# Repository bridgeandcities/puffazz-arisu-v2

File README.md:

# puffazz-arisu-v2
Custom PCB for the Arisu keyboard with LED underglow and USB-C support.

Based from https://github.com/FateNozomi/arisu-pcb

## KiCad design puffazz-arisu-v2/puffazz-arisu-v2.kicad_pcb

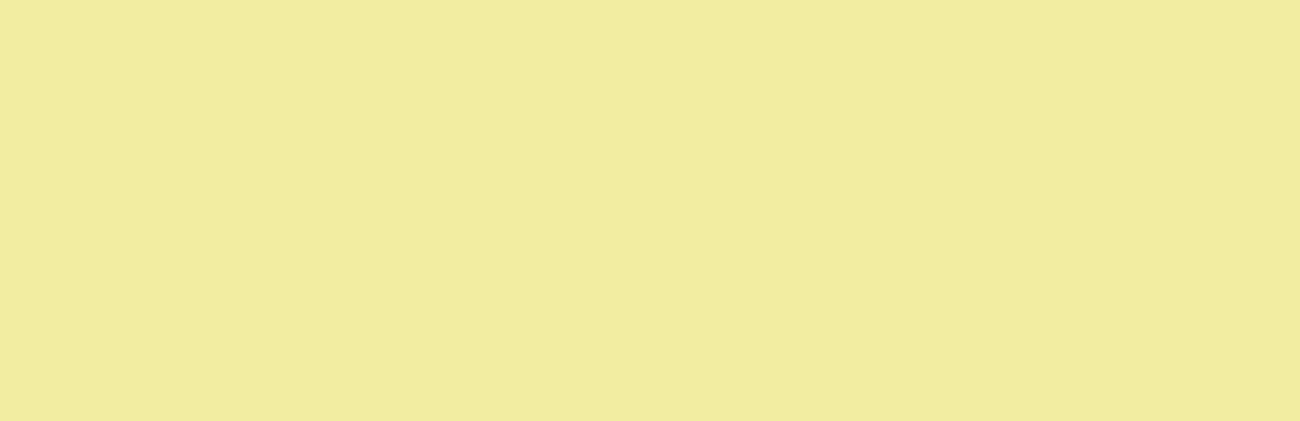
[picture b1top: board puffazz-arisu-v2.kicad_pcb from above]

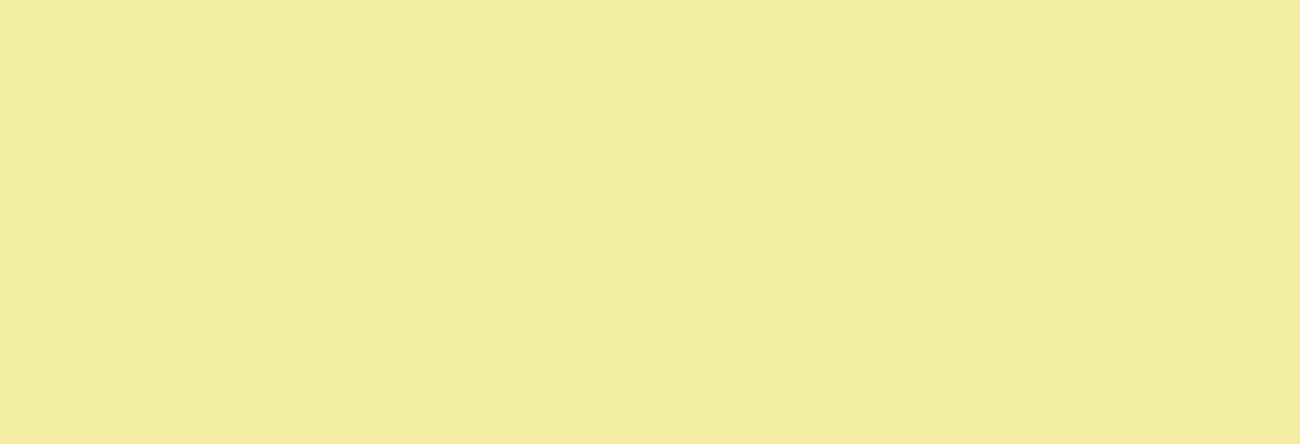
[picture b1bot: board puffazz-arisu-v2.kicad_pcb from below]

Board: 2 copper layers, 96 parts (25 on the bottom side), 39 nets, no tracks yet.

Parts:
C18: 0.1uF; C_0805_2012Metric
D69, D70, D71, D72, D73, D74, D75, D76, D77, D78, D79, D80, D81, D82: WS2812B; LED_WS2812B_PLCC4_5.0x5.0mm_P3.2mm
MX_: SW_Cherry_MX_1.00u_PCB
MX_#0, MX_#1, MX_#2, MX_#3, MX_#4, MX_#5, MX_#6, MX_#7, MX_#8, MX_#9: MX-NoLED; SW_Cherry_MX_1.00u_PCB
MX_#+1: MX-NoLED; SW_Cherry_MX_1.00u_PCB
MX_#-1: MX-NoLED; SW_Cherry_MX_1.00u_PCB
MX_#BKSP2: MX-NoLED; SW_Cherry_MX_2.00u_PCB
MX_#PGUP1: MX-NoLED; SW_Cherry_MX_1.00u_PCB
MX_#TAB1: MX-NoLED; SW_Cherry_MX_1.50u_PCB
MX_#`1: MX-NoLED; SW_Cherry_MX_1.00u_PCB
MX_#|1: MX-NoLED; SW_Cherry_MX_1.00u_PCB
MX_:1: MX-NoLED; SW_Cherry_MX_1.00u_PCB
MX_<1: MX-NoLED; SW_Cherry_MX_1.00u_PCB
MX_>1: MX-NoLED; SW_Cherry_MX_1.00u_PCB
MX_?1: MX-NoLED; SW_Cherry_MX_1.00u_PCB
MX_A1: MX-NoLED; SW_Cherry_MX_1.00u_PCB
MX_B1: MX-NoLED; SW_Cherry_MX_1.00u_PCB
MX_BCKSP1: MX-NoLED; SW_Cherry_MX_1.50u_PCB
MX_C1: MX-NoLED; SW_Cherry_MX_1.00u_PCB
MX_CAPS1: MX-NoLED; SW_Cherry_MX_1.75u_PCB
MX_CAPS2: MX-NoLED; SW_Cherry_MX_1.00u_PCB
MX_D1: MX-NoLED; SW_Cherry_MX_1.00u_PCB
MX_DOWN1: MX-NoLED; SW_Cherry_MX_1.00u_PCB
MX_E1: MX-NoLED; SW_Cherry_MX_1.00u_PCB
MX_ESC1: MX-NoLED; SW_Cherry_MX_1.00u_PCB
MX_F1: MX-NoLED; SW_Cherry_MX_1.00u_PCB
MX_FN1: MX-NoLED; SW_Cherry_MX_1.00u_PCB
MX_G1: MX-NoLED; SW_Cherry_MX_1.00u_PCB
MX_H1: MX-NoLED; SW_Cherry_MX_1.00u_PCB
MX_I1: MX-NoLED; SW_Cherry_MX_1.00u_PCB
MX_J1: MX-NoLED; SW_Cherry_MX_1.00u_PCB
MX_K1: MX-NoLED; SW_Cherry_MX_1.00u_PCB
MX_L1: MX-NoLED; SW_Cherry_MX_1.00u_PCB
MX_LALT1: MX-NoLED; SW_Cherry_MX_1.25u_PCB
MX_LALT2: MX-NoLED; SW_Cherry_MX_1.50u_PCB
MX_LCTRL1: MX-NoLED; SW_Cherry_MX_1.50u_PCB
MX_LEFT1: MX-NoLED; SW_Cherry_MX_1.00u_PCB
MX_LSHIFT1: MX-NoLED; SW_Cherry_MX_2.25u_PCB
MX_LWIN1: MX-NoLED; SW_Cherry_MX_1.00u_PCB
MX_M1: MX-NoLED; SW_Cherry_MX_1.00u_PCB
MX_N1: MX-NoLED; SW_Cherry_MX_1.00u_PCB
MX_O1: MX-NoLED; SW_Cherry_MX_1.00u_PCB
MX_P1: MX-NoLED; SW_Cherry_MX_1.00u_PCB
MX_PGDN1: MX-NoLED; SW_Cherry_MX_1.00u_PCB
MX_Q1: MX-NoLED; SW_Cherry_MX_1.00u_PCB
MX_R1: MX-NoLED; SW_Cherry_MX_1.00u_PCB
MX_RALT1: MX-NoLED; SW_Cherry_MX_1.50u_PCB
MX_RETURN1: MX-NoLED; SW_Cherry_MX_2.25u_PCB_Flipped
MX_RIGHT1: MX-NoLED; SW_Cherry_MX_1.00u_PCB
MX_RSHIFT1: MX-NoLED; SW_Cherry_MX_1.75u_PCB
MX_S1: MX-NoLED; SW_Cherry_MX_1.00u_PCB
MX_SPACE1: MX-NoLED; SW_Cherry_MX_2.00u_PCB_Flipped
MX_SPACE2: MX-NoLED; SW_Cherry_MX_2.25u_PCB_Flipped
MX_SPACE3: MX-NoLED; SW_Cherry_MX_2.75u_PCB_Flipped
MX_T1: MX-NoLED; SW_Cherry_MX_1.00u_PCB
MX_U1: MX-NoLED; SW_Cherry_MX_1.00u_PCB
MX_UP1: MX-NoLED; SW_Cherry_MX_1.00u_PCB
MX_V1: MX-NoLED; SW_Cherry_MX_1.00u_PCB
MX_W1: MX-NoLED; SW_Cherry_MX_1.00u_PCB
MX_X1: MX-NoLED; SW_Cherry_MX_1.00u_PCB
MX_Y1: MX-NoLED; SW_Cherry_MX_1.00u_PCB
MX_Z1: MX-NoLED; SW_Cherry_MX_1.00u_PCB
MX_[1: MX-NoLED; SW_Cherry_MX_1.00u_PCB
MX_]1: MX-NoLED; SW_Cherry_MX_1.00u_PCB
R1, R2: 10k; R_0805_2012Metric
R3, R4: 5.1k; R_0805_2012Metric
R5, R6: 22; R_0805_2012Metric
SW1: SW_Push; SW_SPST_SKQG_WithStem
U1: ATmega32U4-AU; TQFP-44_10x10mm_P0.8mm
USB1: HRO-TYPE-C-31-M-12; HRO-TYPE-C-31-M-12-Assembly
Y1: 16MHz; Crystal_SMD_3225-4Pin_3.2x2.5mm_HandSoldering

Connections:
+5V: C18.1, D69.1, D70.1, D71.1, D72.1, D73.1, D74.1, D75.1, D76.1, D77.1, D78.1, D79.1, D80.1, D81.1, D82.1, R1.2, U1.2, U1.7, U1.14, U1.24, U1.34, U1.44
COL0: MX_#1.1, MX_#TAB1.1, MX_A1.1, MX_CAPS1.1, MX_CAPS2.1, MX_ESC1.1, MX_LCTRL1.1, MX_LSHIFT1.1, MX_Q1.1, MX_Z1.1, U1.41
COL1: MX_#2.1, MX_#3.1, MX_C1.1, MX_D1.1, MX_E1.1, MX_LALT1.1, MX_LALT2.1, MX_S1.1, MX_W1.1, MX_X1.1, U1.40
COL2: MX_#4.1, MX_#5.1, MX_B1.1, MX_F1.1, MX_G1.1, MX_LWIN1.1, MX_R1.1, MX_SPACE1.1, MX_SPACE2.1, MX_T1.1, MX_V1.1, U1.39
COL3: MX_#6.1, MX_#7.1, MX_H1.1, MX_J1.1, MX_M1.1, MX_N1.1, MX_SPACE3.1, MX_U1.1, MX_Y1.1, U1.27
COL4: MX_#8.1, MX_#9.1, MX_<1.1, MX_>1.1, MX_I1.1, MX_K1.1, MX_L1.1, MX_O1.1, MX_RALT1.1, U1.21
COL5: MX_#0.1, MX_#-1.1, MX_:1.1, MX_?1.1, MX_LEFT1.1, MX_P1.1, MX_RSHIFT1.1, MX_[1.1, U1.20
COL6: MX_#+1.1, MX_#`1.1, MX_DOWN1.1, MX_RETURN1.1, MX_UP1.1, MX_]1.1, U1.19
COL7: MX_#BKSP2.1, MX_#PGUP1.1, MX_#|1.1, MX_BCKSP1.1, MX_FN1.1, MX_PGDN1.1, MX_RIGHT1.1, U1.18
D+: R5.2, U1.4
D-: R6.2, U1.3
GND: C18.2, D69.3, D70.3, D71.3, D72.3, D73.3, D74.3, D75.3, D76.3, D77.3, D78.3, D79.3, D80.3, D81.3, D82.3, R2.1, R3.1, R4.1, SW1.1, U1.5, U1.15, U1.23, U1.35, U1.43, USB1.1, USB1.12, USB1.13, Y1.2, Y1.4
unnamed: U1.17, Y1.1
unnamed: U1.16, Y1.3
unnamed: R5.1, USB1.5, USB1.7
unnamed: R6.1, USB1.6, USB1.8
unnamed: MX_#BKSP2.2, MX_#|1.2
unnamed: MX_CAPS1.2, MX_CAPS2.2
unnamed: MX_LALT1.2, MX_LALT2.2
unnamed: MX_SPACE1.2, MX_SPACE2.2
unnamed: D69.2, D70.4
unnamed: D70.2, D71.4
unnamed: D71.2, D72.4
unnamed: D72.2, D73.4
unnamed: D73.2, D74.4
unnamed: D74.2, D75.4
unnamed: D75.2, D76.4
unnamed: D76.2, D77.4
unnamed: D77.2, D78.4
unnamed: D78.2, D79.4
unnamed: D79.2, D80.4
unnamed: D80.2, D81.4
unnamed: D81.2, D82.4
unnamed: R1.1, SW1.2, U1.13
unnamed: R2.2, U1.33
unnamed: R3.2, USB1.4
unnamed: R4.2, USB1.10
RGBLED: D69.4, U1.12
VCC: USB1.2, USB1.11

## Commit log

2020-08-02 Added submodules
2020-08-03 Completed full schematic draft without matrix labels on the MCU
2020-08-27 Finished scematic
2020-08-28 Finished placing switch footprints on to the pcb
2020-08-28 Fixed usb-c footprint not working with rats nest view
2020-08-29 Finished routing switches and RGB LED
2020-08-29 Completed placing all components, missing some 5V routes.
2020-08-30 Finished routing all the components
2020-08-30 Added ground fills to the MCU, crystal and USB-C port
2020-09-03 Tidied up underglow RGB traces
2020-09-06 Fixed overall issues, added decorations to the board and generated gerbers
2020-09-07 Fixed small issues and swapped LED to WS2812B
